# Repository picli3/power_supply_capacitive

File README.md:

# power_supply_capacitive

Fuente de alimentación capacitiva para aplicaciones de baja potencia, orientada a soluciones compactas conectadas a red con las debidas precauciones.

## Qué incluye
- esquemáticos o archivos de diseño en KiCad
- PCB o documentación asociada
- base reutilizable para análisis, fabricación o mejora del proyecto

## Propósito general
Este repositorio busca concentrar el diseño de hardware del proyecto en un formato editable y reutilizable, facilitando pruebas, documentación y futuras iteraciones del circuito.

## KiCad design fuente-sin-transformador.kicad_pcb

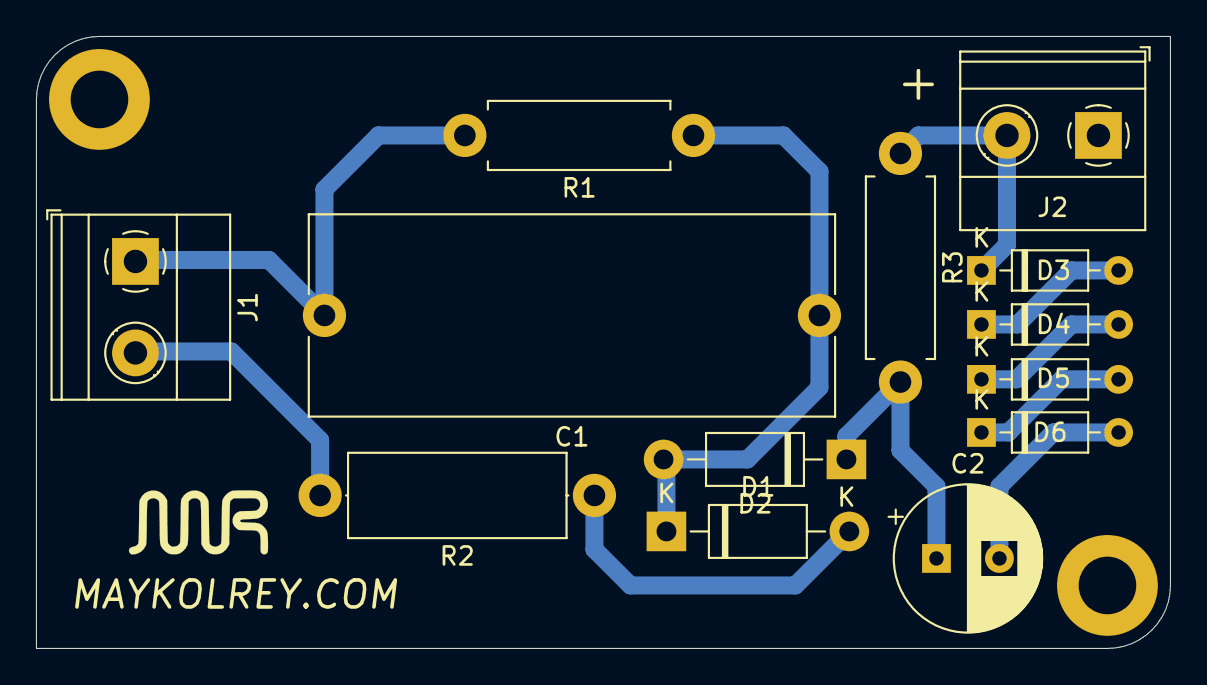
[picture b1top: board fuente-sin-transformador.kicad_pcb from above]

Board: 2 copper layers, 63.0 x 34.0 mm, 15 parts (0 on the bottom side), 9 nets.

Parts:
C1: 2.2uF; C_Rect_L29.0mm_W11.0mm_P27.50mm_MKT
C2: 470uF; CP_Radial_D8.0mm_P3.50mm
D1, D2: 1N4004; D_DO-41_SOD81_P10.16mm_Horizontal
D3, D4, D5, D6: 1N5225B-TAP; D_DO-35_SOD27_P7.62mm_Horizontal
J1: in; TerminalBlock_Phoenix_MKDS-1,5-2-5.08_1x02_P5.08mm_Horizont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
J2: out; TerminalBlock_Phoenix_MKDS-1,5-2-5.08_1x02_P5.08mm_Horizont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
J3, J4: MH; MountingHole_3.2mm_M3_DIN965_Pad
R1: 120K; R_Axial_DIN0411_L9.9mm_D3.6mm_P12.70mm_Horizontal
R2: 33; R_Axial_DIN0414_L11.9mm_D4.5mm_P15.24mm_Horizontal
R3: 100; R_Axial_DIN0411_L9.9mm_D3.6mm_P12.70mm_Horizontal

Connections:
+12V: D3.1, J2.2, R3.1
/VAC: C1.2, J1.1, R1.2
GNDREF: C2.2, D1.2, D6.2, J2.1, J3.1, J4.1, R2.1
unnamed: C1.1, D1.1, D2.2, R1.1
unnamed: C2.1, D2.1, R3.2
unnamed: D3.2, D4.1
unnamed: D4.2, D5.1
unnamed: D5.2, D6.1
unnamed: J1.2, R2.2

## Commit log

2020-09-05 fuente capacitiva 12V no probada
2026-04-29 Agrega README con descripción inicial del proyecto
